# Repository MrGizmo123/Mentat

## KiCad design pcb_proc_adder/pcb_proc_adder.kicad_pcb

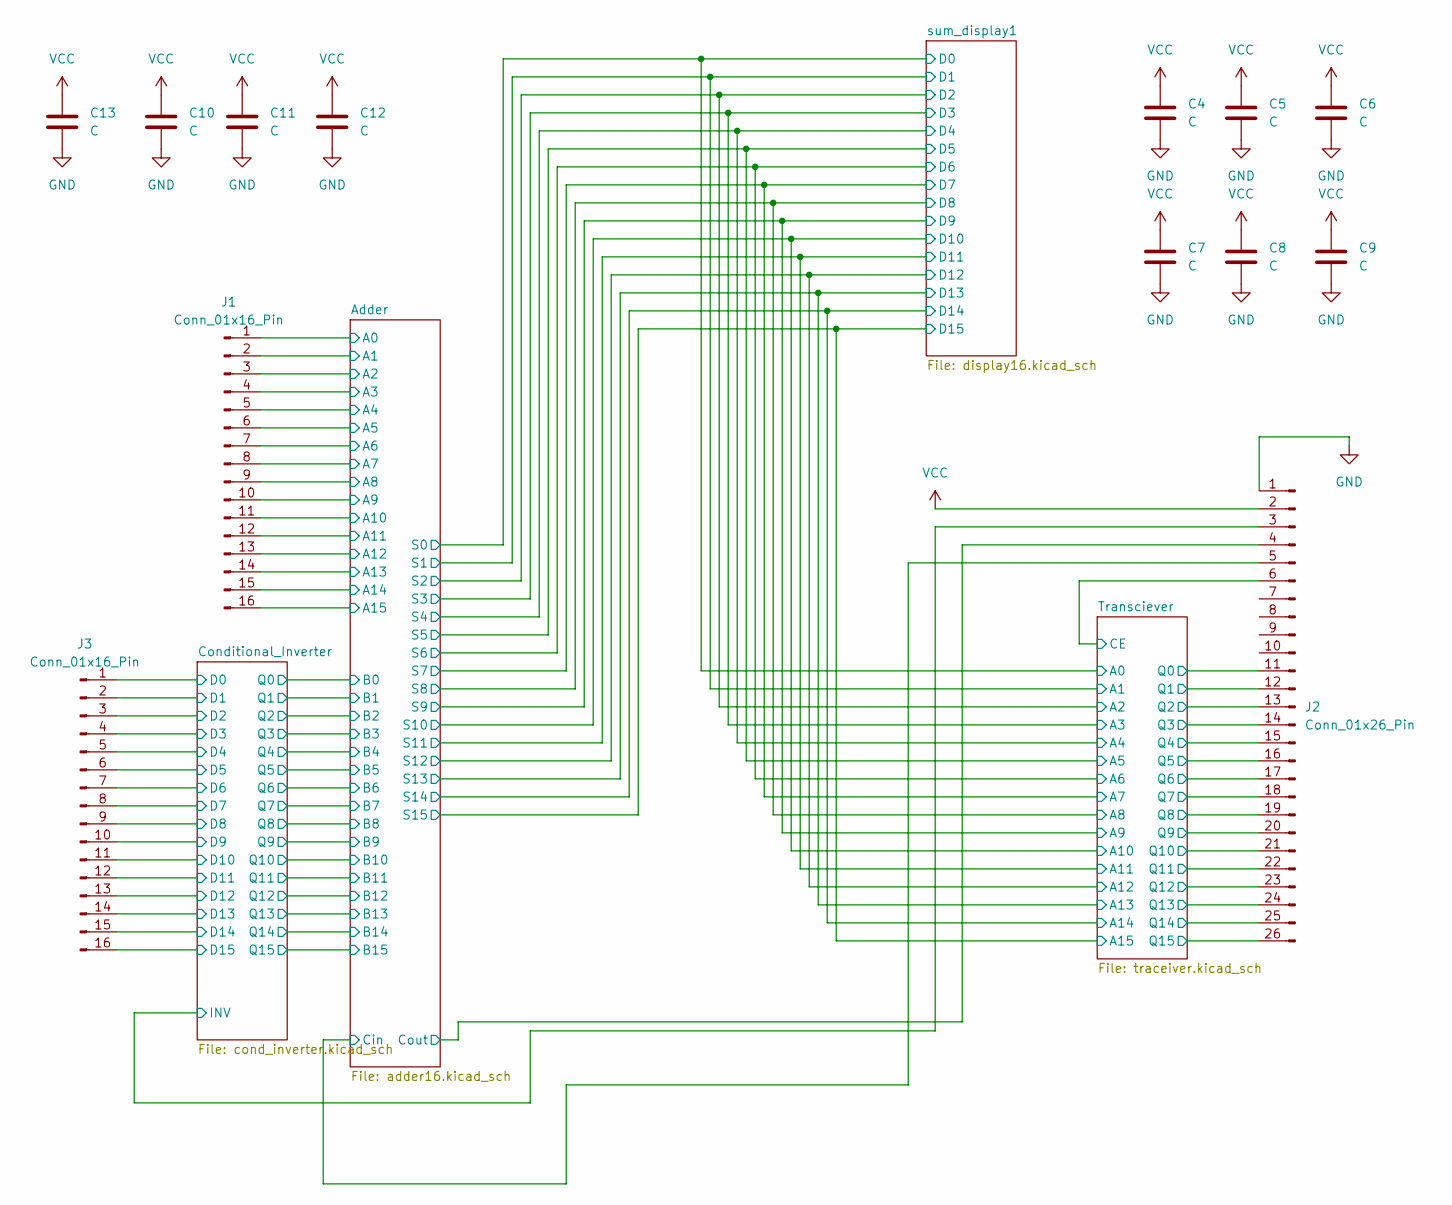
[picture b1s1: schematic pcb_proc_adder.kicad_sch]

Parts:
C4, C5, C6, C7, C8, C9, C10, C11, C12, C13: C; C_0805_2012Metric
J1, J3: Conn_01x16_Pin; PinHeader_1x16_P2.54mm_Vertical
J2: Conn_01x26_Pin; PinHeader_1x26_P2.54mm_Horizontal

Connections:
/Adder/A0: J1.1; also elsewhere on the board
/Adder/A1: J1.2; also elsewhere on the board
/Adder/A2: J1.3; also elsewhere on the board
/Adder/A3: J1.4; also elsewhere on the board
/Adder/A4: J1.5; also elsewhere on the board
/Adder/A5: J1.6; also elsewhere on the board
/Adder/A6: J1.7; also elsewhere on the board
/Adder/A7: J1.8; also elsewhere on the board
/Adder/A8: J1.9; also elsewhere on the board
/Adder/A9: J1.10; also elsewhere on the board
/Adder/A10: J1.11; also elsewhere on the board
/Adder/A11: J1.12; also elsewhere on the board
/Adder/A12: J1.13; also elsewhere on the board
/Adder/A13: J1.14; also elsewhere on the board
/Adder/A14: J1.15; also elsewhere on the board
/Adder/A15: J1.16; also elsewhere on the board
/Adder/Cin: J2.5; also elsewhere on the board
/Adder/Cout: J2.4; also elsewhere on the board
/Conditional_Inverter/D0: J3.1; also elsewhere on the board
/Conditional_Inverter/D1: J3.2; also elsewhere on the board
/Conditional_Inverter/D2: J3.3; also elsewhere on the board
/Conditional_Inverter/D3: J3.4; also elsewhere on the board
/Conditional_Inverter/D4: J3.5; also elsewhere on the board
/Conditional_Inverter/D5: J3.6; also elsewhere on the board
/Conditional_Inverter/D6: J3.7; also elsewhere on the board
/Conditional_Inverter/D7: J3.8; also elsewhere on the board
/Conditional_Inverter/D8: J3.9; also elsewhere on the board
/Conditional_Inverter/D9: J3.10; also elsewhere on the board
/Conditional_Inverter/D10: J3.11; also elsewhere on the board
/Conditional_Inverter/D11: J3.12; also elsewhere on the board
/Conditional_Inverter/D12: J3.13; also elsewhere on the board
/Conditional_Inverter/D13: J3.14; also elsewhere on the board
/Conditional_Inverter/D14: J3.15; also elsewhere on the board
/Conditional_Inverter/D15: J3.16; also elsewhere on the board
/Conditional_Inverter/INV: J2.3; also elsewhere on the board
/Transciever/CE: J2.6; also elsewhere on the board
/Transciever/Q0: J2.11; also elsewhere on the board
/Transciever/Q1: J2.12; also elsewhere on the board
/Transciever/Q2: J2.13; also elsewhere on the board
/Transciever/Q3: J2.14; also elsewhere on the board
/Transciever/Q4: J2.15; also elsewhere on the board
/Transciever/Q5: J2.16; also elsewhere on the board
/Transciever/Q6: J2.17; also elsewhere on the board
/Transciever/Q7: J2.18; also elsewhere on the board
/Transciever/Q8: J2.19; also elsewhere on the board
/Transciever/Q9: J2.20; also elsewhere on the board
/Transciever/Q10: J2.21; also elsewhere on the board
/Transciever/Q11: J2.22; also elsewhere on the board
/Transciever/Q12: J2.23; also elsewhere on the board
/Transciever/Q13: J2.24; also elsewhere on the board
/Transciever/Q14: J2.25; also elsewhere on the board
/Transciever/Q15: J2.26; also elsewhere on the board
GND: C4.2, C5.2, C6.2, C7.2, C8.2, C9.2, C10.2, C11.2, C12.2, C13.2, J2.1; also elsewhere on the board
VCC: C4.1, C5.1, C6.1, C7.1, C8.1, C9.1, C10.1, C11.1, C12.1, C13.1, J2.2; also elsewhere on the board

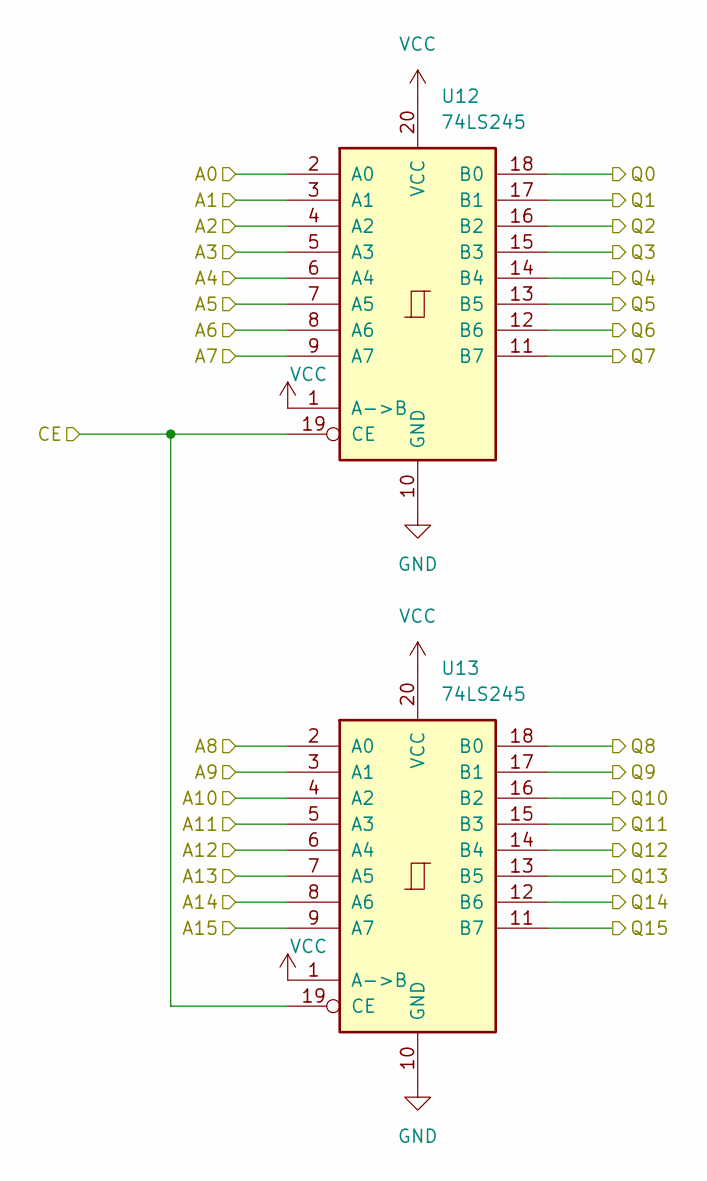
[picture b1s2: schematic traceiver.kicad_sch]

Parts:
U12, U13: 74LS245; DIP-20_W7.62mm_LongPads

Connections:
/Adder/S0: U12.2 (A0); also elsewhere on the board
/Adder/S1: U12.3 (A1); also elsewhere on the board
/Adder/S2: U12.4 (A2); also elsewhere on the board
/Adder/S3: U12.5 (A3); also elsewhere on the board
/Adder/S4: U12.6 (A4); also elsewhere on the board
/Adder/S5: U12.7 (A5); also elsewhere on the board
/Adder/S6: U12.8 (A6); also elsewhere on the board
/Adder/S7: U12.9 (A7); also elsewhere on the board
/Adder/S8: U13.2 (A0); also elsewhere on the board
/Adder/S9: U13.3 (A1); also elsewhere on the board
/Adder/S10: U13.4 (A2); also elsewhere on the board
/Adder/S11: U13.5 (A3); also elsewhere on the board
/Adder/S12: U13.6 (A4); also elsewhere on the board
/Adder/S13: U13.7 (A5); also elsewhere on the board
/Adder/S14: U13.8 (A6); also elsewhere on the board
/Adder/S15: U13.9 (A7); also elsewhere on the board
/Transciever/CE: U12.19 (CE), U13.19 (CE); also elsewhere on the board
/Transciever/Q0: U12.18 (B0); also elsewhere on the board
/Transciever/Q1: U12.17 (B1); also elsewhere on the board
/Transciever/Q2: U12.16 (B2); also elsewhere on the board
/Transciever/Q3: U12.15 (B3); also elsewhere on the board
/Transciever/Q4: U12.14 (B4); also elsewhere on the board
/Transciever/Q5: U12.13 (B5); also elsewhere on the board
/Transciever/Q6: U12.12 (B6); also elsewhere on the board
/Transciever/Q7: U12.11 (B7); also elsewhere on the board
/Transciever/Q8: U13.18 (B0); also elsewhere on the board
/Transciever/Q9: U13.17 (B1); also elsewhere on the board
/Transciever/Q10: U13.16 (B2); also elsewhere on the board
/Transciever/Q11: U13.15 (B3); also elsewhere on the board
/Transciever/Q12: U13.14 (B4); also elsewhere on the board
/Transciever/Q13: U13.13 (B5); also elsewhere on the board
/Transciever/Q14: U13.12 (B6); also elsewhere on the board
/Transciever/Q15: U13.11 (B7); also elsewhere on the board
GND: U12.10 (GND), U13.10 (GND); also elsewhere on the board
VCC: U12.1 (A->B), U12.20 (VCC), U13.1 (A->B), U13.20 (VCC); also elsewhere on the board

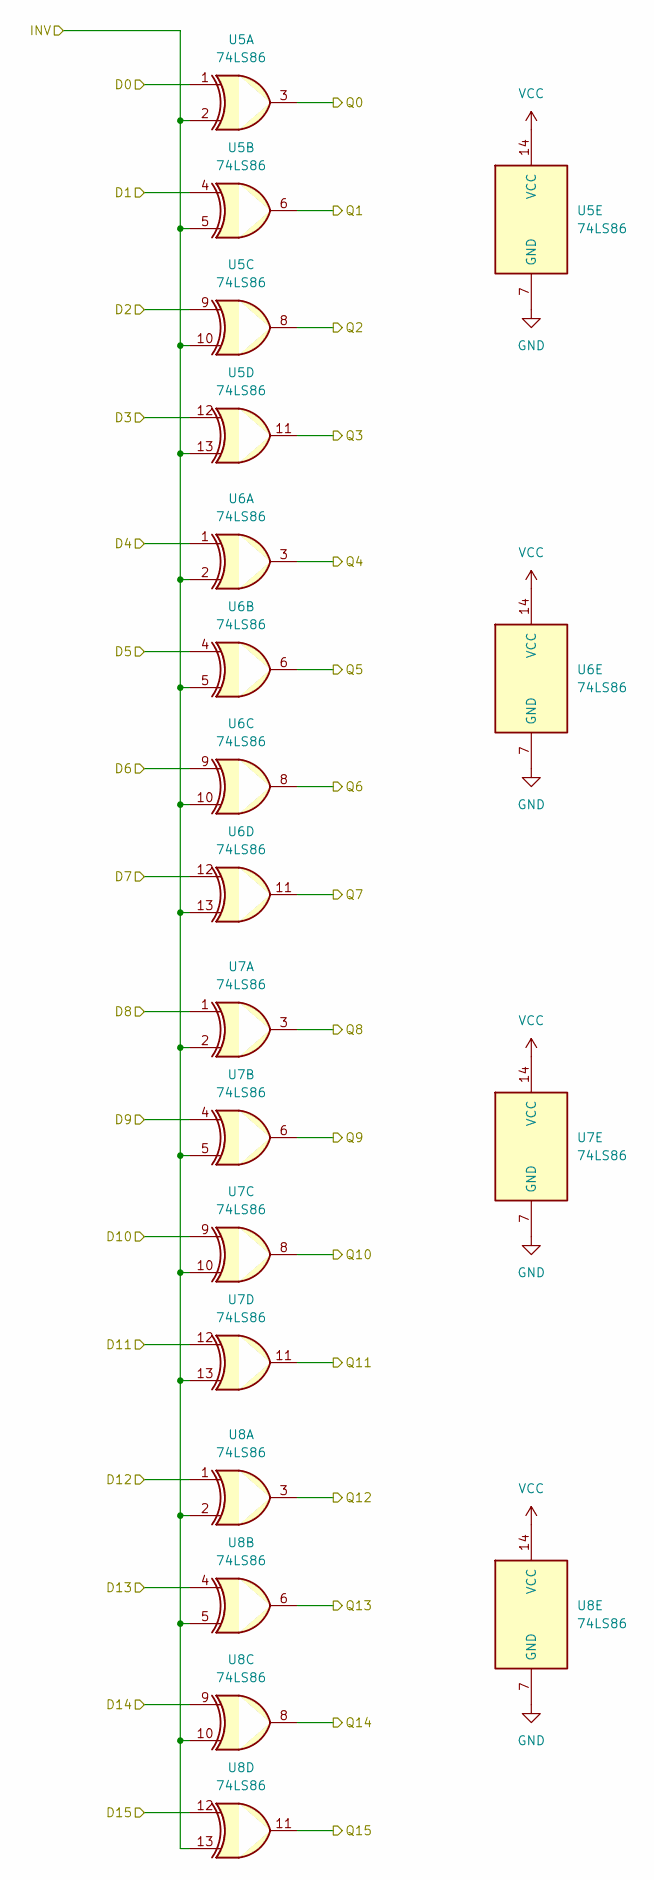
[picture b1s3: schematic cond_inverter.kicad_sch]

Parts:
U5, U6, U7, U8: 74LS86; DIP-14_W7.62mm_LongPads

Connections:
/Adder/B0: U5.3; also elsewhere on the board
/Adder/B1: U5.6; also elsewhere on the board
/Adder/B2: U5.8; also elsewhere on the board
/Adder/B3: U5.11; also elsewhere on the board
/Adder/B4: U6.3; also elsewhere on the board
/Adder/B5: U6.6; also elsewhere on the board
/Adder/B6: U6.8; also elsewhere on the board
/Adder/B7: U6.11; also elsewhere on the board
/Adder/B8: U7.3; also elsewhere on the board
/Adder/B9: U7.6; also elsewhere on the board
/Adder/B10: U7.8; also elsewhere on the board
/Adder/B11: U7.11; also elsewhere on the board
/Adder/B12: U8.3; also elsewhere on the board
/Adder/B13: U8.6; also elsewhere on the board
/Adder/B14: U8.8; also elsewhere on the board
/Adder/B15: U8.11; also elsewhere on the board
/Conditional_Inverter/D0: U5.1; also elsewhere on the board
/Conditional_Inverter/D1: U5.4; also elsewhere on the board
/Conditional_Inverter/D2: U5.9; also elsewhere on the board
/Conditional_Inverter/D3: U5.12; also elsewhere on the board
/Conditional_Inverter/D4: U6.1; also elsewhere on the board
/Conditional_Inverter/D5: U6.4; also elsewhere on the board
/Conditional_Inverter/D6: U6.9; also elsewhere on the board
/Conditional_Inverter/D7: U6.12; also elsewhere on the board
/Conditional_Inverter/D8: U7.1; also elsewhere on the board
/Conditional_Inverter/D9: U7.4; also elsewhere on the board
/Conditional_Inverter/D10: U7.9; also elsewhere on the board
/Conditional_Inverter/D11: U7.12; also elsewhere on the board
/Conditional_Inverter/D12: U8.1; also elsewhere on the board
/Conditional_Inverter/D13: U8.4; also elsewhere on the board
/Conditional_Inverter/D14: U8.9; also elsewhere on the board
/Conditional_Inverter/D15: U8.12; also elsewhere on the board
/Conditional_Inverter/INV: U5.2, U5.5, U5.10, U5.13, U6.2, U6.5, U6.10, U6.13, U7.2, U7.5, U7.10, U7.13, U8.2, U8.5, U8.10, U8.13; also elsewhere on the board
GND: U5.7 (GND), U6.7 (GND), U7.7 (GND), U8.7 (GND); also elsewhere on the board
VCC: U5.14 (VCC), U6.14 (VCC), U7.14 (VCC), U8.14 (VCC); also elsewhere on the board

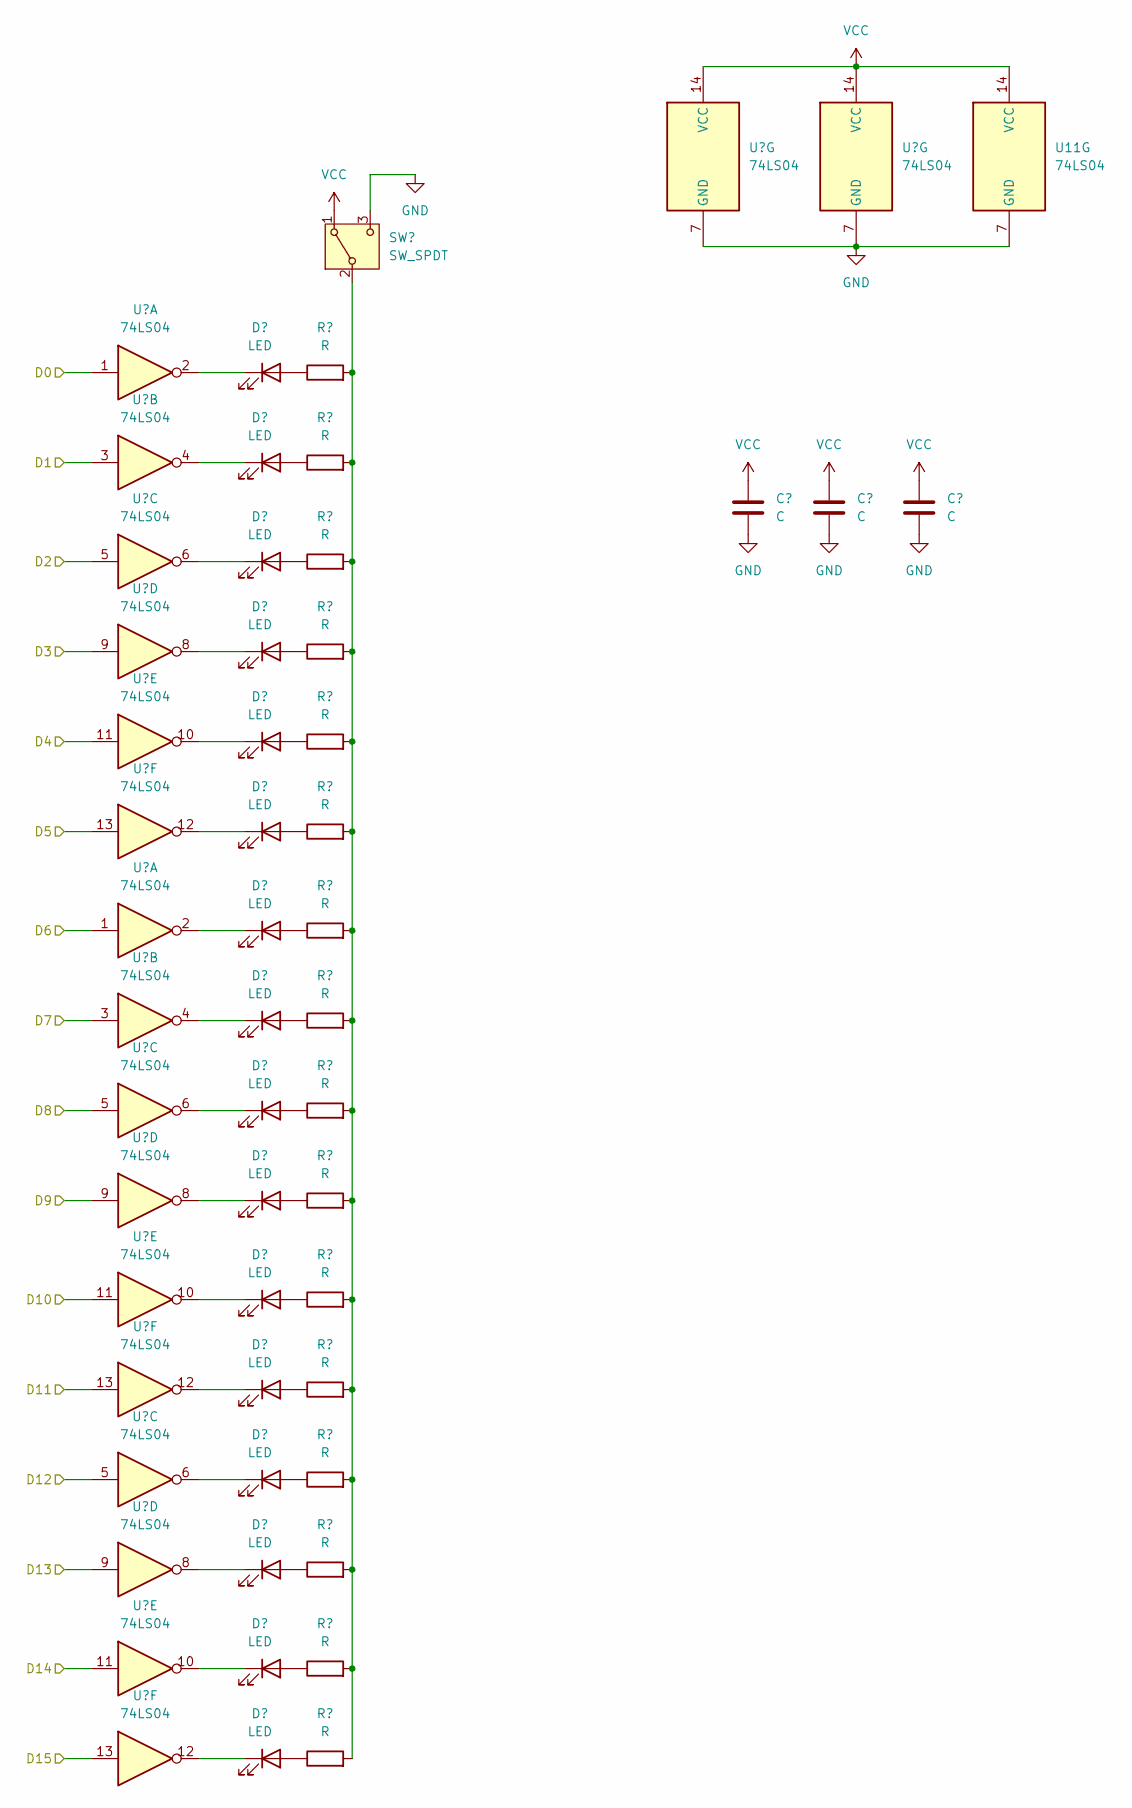
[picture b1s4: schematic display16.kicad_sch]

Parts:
C1, C2, C3: C; C_0805_2012Metric
D1, D2, D3, D4, D5, D6, D7, D8, D9, D10, D11, D12, D13, D14, D15, D16: LED; LED_Rectangular_W5.0mm_H2.0mm
R1, R2, R3, R4, R5, R6, R7, R8, R9, R10, R11, R12, R13, R14, R15, R16: R; R_0805_2012Metric
SW1: SW_SPDT; SW_E-Switch_EG1271_SPDT
U9: 74LS04; DIP-14_W7.62mm_Socket_LongPads
U10, U11: 74LS04; DIP-14_W7.62mm_LongPads

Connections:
/Adder/S0: U9.1; also elsewhere on the board
/Adder/S1: U9.3; also elsewhere on the board
/Adder/S2: U9.5; also elsewhere on the board
/Adder/S3: U9.9; also elsewhere on the board
/Adder/S4: U9.11; also elsewhere on the board
/Adder/S5: U9.13; also elsewhere on the board
/Adder/S6: U10.1; also elsewhere on the board
/Adder/S7: U10.3; also elsewhere on the board
/Adder/S8: U10.5; also elsewhere on the board
/Adder/S9: U10.9; also elsewhere on the board
/Adder/S10: U10.11; also elsewhere on the board
/Adder/S11: U10.13; also elsewhere on the board
/Adder/S12: U11.5; also elsewhere on the board
/Adder/S13: U11.9; also elsewhere on the board
/Adder/S14: U11.11; also elsewhere on the board
/Adder/S15: U11.13; also elsewhere on the board
GND: C1.2, C2.2, C3.2, SW1.3 (C), U9.7 (GND), U10.7 (GND), U11.7 (GND); also elsewhere on the board
unnamed: D1.2 (A), R1.1
unnamed: D1.1 (K), U9.2
unnamed: D2.2 (A), R2.1
unnamed: D2.1 (K), U9.4
unnamed: D3.2 (A), R3.1
unnamed: D3.1 (K), U9.6
unnamed: D4.2 (A), R4.1
unnamed: D4.1 (K), U9.8
unnamed: D5.2 (A), R5.1
unnamed: D5.1 (K), U9.10
unnamed: D6.2 (A), R6.1
unnamed: D6.1 (K), U9.12
unnamed: D7.2 (A), R7.1
unnamed: D7.1 (K), U10.2
unnamed: D8.2 (A), R8.1
unnamed: D8.1 (K), U10.4
unnamed: D9.2 (A), R9.1
unnamed: D9.1 (K), U10.6
unnamed: D10.2 (A), R10.1
unnamed: D10.1 (K), U10.8
unnamed: D11.2 (A), R11.1
unnamed: D11.1 (K), U10.10
unnamed: D12.2 (A), R12.1
unnamed: D12.1 (K), U10.12
unnamed: D13.2 (A), R13.1
unnamed: D13.1 (K), U11.6
unnamed: D14.2 (A), R14.1
unnamed: D14.1 (K), U11.8
unnamed: D15.2 (A), R15.1
unnamed: D15.1 (K), U11.10
unnamed: D16.2 (A), R16.1
unnamed: D16.1 (K), U11.12
unnamed: R1.2, R2.2, R3.2, R4.2, R5.2, R6.2, R7.2, R8.2, R9.2, R10.2, R11.2, R12.2, R13.2, R14.2, R15.2, R16.2, SW1.2 (B)
VCC: C1.1, C2.1, C3.1, SW1.1 (A), U9.14 (VCC), U10.14 (VCC), U11.14 (VCC); also elsewhere on the board

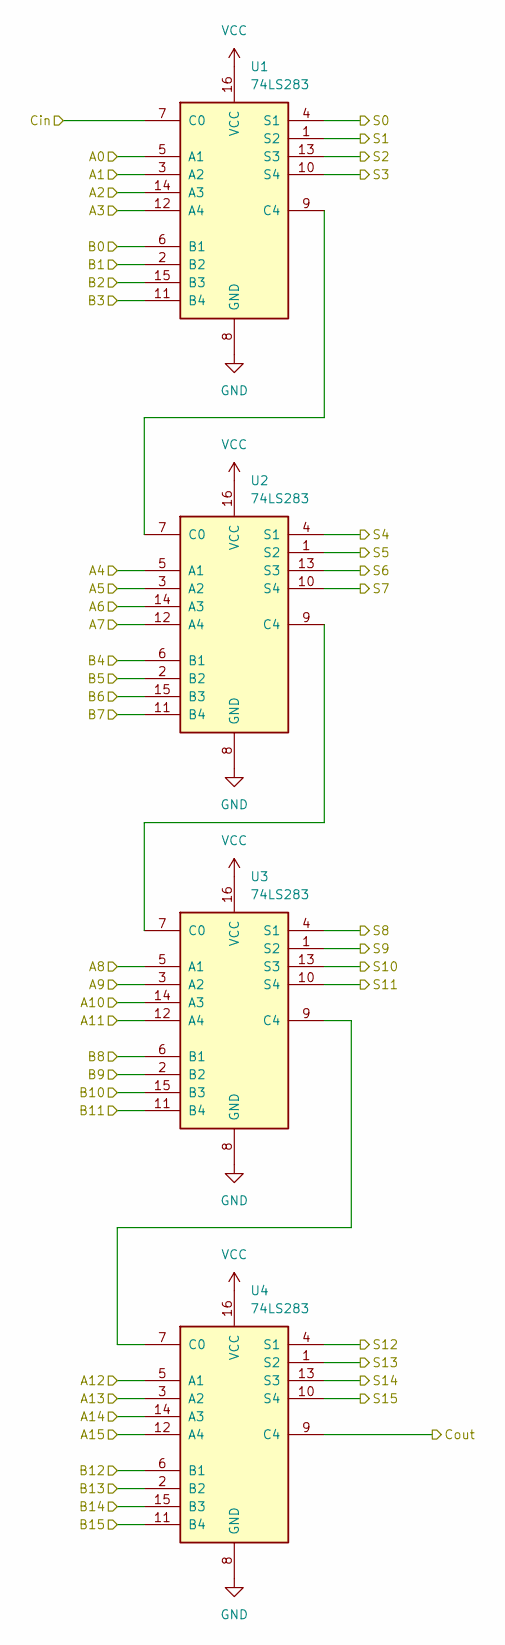
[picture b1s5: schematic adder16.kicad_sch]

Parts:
U1, U2, U3, U4: 74LS283; DIP-16_W7.62mm_LongPads

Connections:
/Adder/A0: U1.5 (A1); also elsewhere on the board
/Adder/A1: U1.3 (A2); also elsewhere on the board
/Adder/A2: U1.14 (A3); also elsewhere on the board
/Adder/A3: U1.12 (A4); also elsewhere on the board
/Adder/A4: U2.5 (A1); also elsewhere on the board
/Adder/A5: U2.3 (A2); also elsewhere on the board
/Adder/A6: U2.14 (A3); also elsewhere on the board
/Adder/A7: U2.12 (A4); also elsewhere on the board
/Adder/A8: U3.5 (A1); also elsewhere on the board
/Adder/A9: U3.3 (A2); also elsewhere on the board
/Adder/A10: U3.14 (A3); also elsewhere on the board
/Adder/A11: U3.12 (A4); also elsewhere on the board
/Adder/A12: U4.5 (A1); also elsewhere on the board
/Adder/A13: U4.3 (A2); also elsewhere on the board
/Adder/A14: U4.14 (A3); also elsewhere on the board
/Adder/A15: U4.12 (A4); also elsewhere on the board
/Adder/B0: U1.6 (B1); also elsewhere on the board
/Adder/B1: U1.2 (B2); also elsewhere on the board
/Adder/B2: U1.15 (B3); also elsewhere on the board
/Adder/B3: U1.11 (B4); also elsewhere on the board
/Adder/B4: U2.6 (B1); also elsewhere on the board
/Adder/B5: U2.2 (B2); also elsewhere on the board
/Adder/B6: U2.15 (B3); also elsewhere on the board
/Adder/B7: U2.11 (B4); also elsewhere on the board
/Adder/B8: U3.6 (B1); also elsewhere on the board
/Adder/B9: U3.2 (B2); also elsewhere on the board
/Adder/B10: U3.15 (B3); also elsewhere on the board
/Adder/B11: U3.11 (B4); also elsewhere on the board
/Adder/B12: U4.6 (B1); also elsewhere on the board
/Adder/B13: U4.2 (B2); also elsewhere on the board
/Adder/B14: U4.15 (B3); also elsewhere on the board
/Adder/B15: U4.11 (B4); also elsewhere on the board
/Adder/Cin: U1.7 (C0); also elsewhere on the board
/Adder/Cout: U4.9 (C4); also elsewhere on the board
/Adder/S0: U1.4 (S1); also elsewhere on the board
/Adder/S1: U1.1 (S2); also elsewhere on the board
/Adder/S2: U1.13 (S3); also elsewhere on the board
/Adder/S3: U1.10 (S4); also elsewhere on the board
/Adder/S4: U2.4 (S1); also elsewhere on the board
/Adder/S5: U2.1 (S2); also elsewhere on the board
/Adder/S6: U2.13 (S3); also elsewhere on the board
/Adder/S7: U2.10 (S4); also elsewhere on the board
/Adder/S8: U3.4 (S1); also elsewhere on the board
/Adder/S9: U3.1 (S2); also elsewhere on the board
/Adder/S10: U3.13 (S3); also elsewhere on the board
/Adder/S11: U3.10 (S4); also elsewhere on the board
/Adder/S12: U4.4 (S1); also elsewhere on the board
/Adder/S13: U4.1 (S2); also elsewhere on the board
/Adder/S14: U4.13 (S3); also elsewhere on the board
/Adder/S15: U4.10 (S4); also elsewhere on the board
GND: U1.8 (GND), U2.8 (GND), U3.8 (GND), U4.8 (GND); also elsewhere on the board
unnamed: U1.9 (C4), U2.7 (C0)
unnamed: U2.9 (C4), U3.7 (C0)
unnamed: U3.9 (C4), U4.7 (C0)
VCC: U1.16 (VCC), U2.16 (VCC), U3.16 (VCC), U4.16 (VCC); also elsewhere on the board

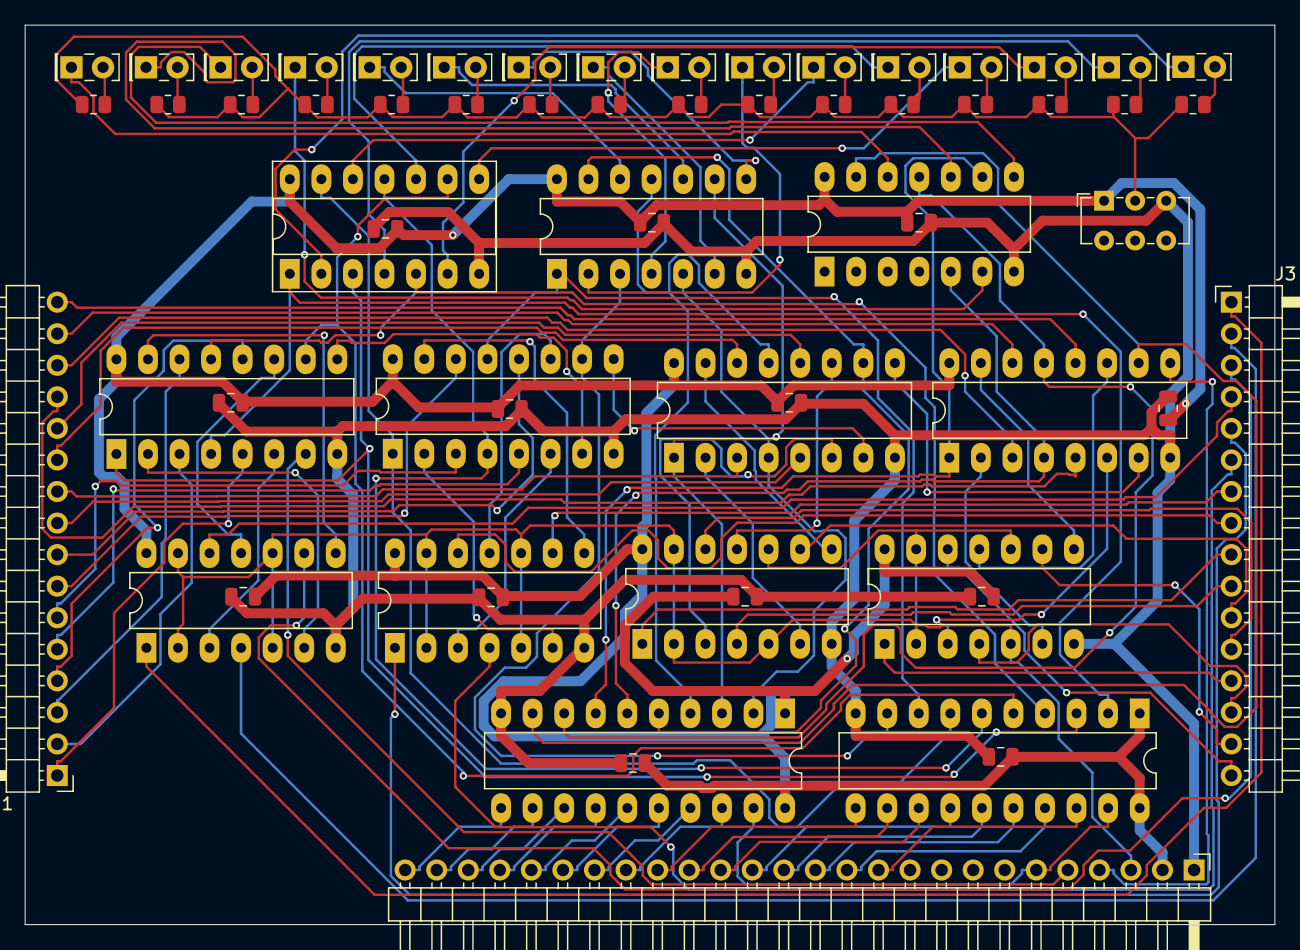
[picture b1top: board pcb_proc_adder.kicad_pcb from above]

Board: 2 copper layers, 100.6 x 72.4 mm, 62 parts (0 on the bottom side), 122 nets.

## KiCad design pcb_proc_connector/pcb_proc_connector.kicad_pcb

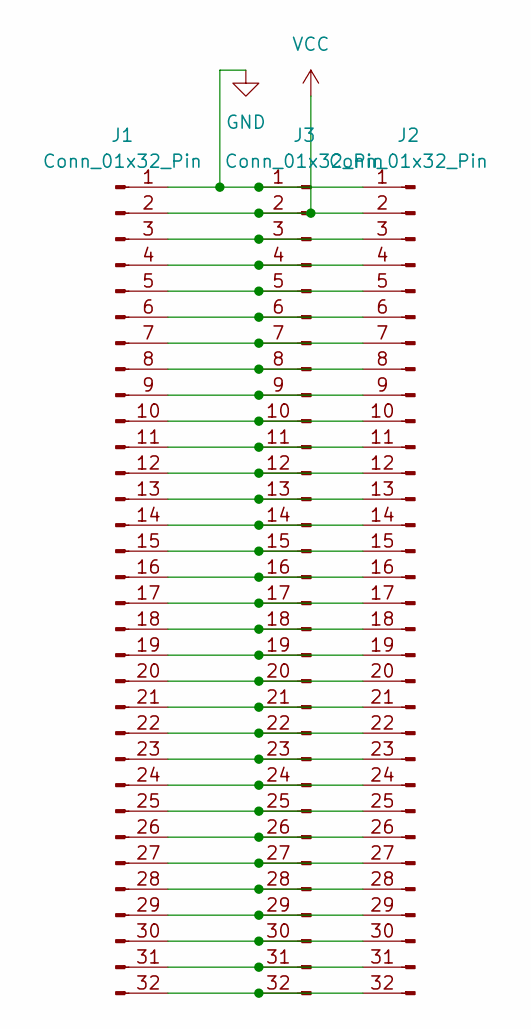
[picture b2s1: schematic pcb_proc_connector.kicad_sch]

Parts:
J1, J2, J3: Conn_01x32_Pin; PinSocket_2x16_P2.54mm_Vertical

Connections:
GND: J1.1, J2.1, J3.1
unnamed: J1.3, J2.3, J3.3
unnamed: J1.4, J2.4, J3.4
unnamed: J1.5, J2.5, J3.5
unnamed: J1.6, J2.6, J3.6
unnamed: J1.7, J2.7, J3.7
unnamed: J1.8, J2.8, J3.8
unnamed: J1.9, J2.9, J3.9
unnamed: J1.10, J2.10, J3.10
unnamed: J1.11, J2.11, J3.11
unnamed: J1.12, J2.12, J3.12
unnamed: J1.13, J2.13, J3.13
unnamed: J1.14, J2.14, J3.14
unnamed: J1.15, J2.15, J3.15
unnamed: J1.16, J2.16, J3.16
unnamed: J1.17, J2.17, J3.17
unnamed: J1.18, J2.18, J3.18
unnamed: J1.19, J2.19, J3.19
unnamed: J1.20, J2.20, J3.20
unnamed: J1.21, J2.21, J3.21
unnamed: J1.22, J2.22, J3.22
unnamed: J1.23, J2.23, J3.23
unnamed: J1.24, J2.24, J3.24
unnamed: J1.25, J2.25, J3.25
unnamed: J1.26, J2.26, J3.26
unnamed: J1.27, J2.27, J3.27
unnamed: J1.28, J2.28, J3.28
unnamed: J1.29, J2.29, J3.29
unnamed: J1.30, J2.30, J3.30
unnamed: J1.31, J2.31, J3.31
unnamed: J1.32, J2.32, J3.32
VCC: J1.2, J2.2, J3.2

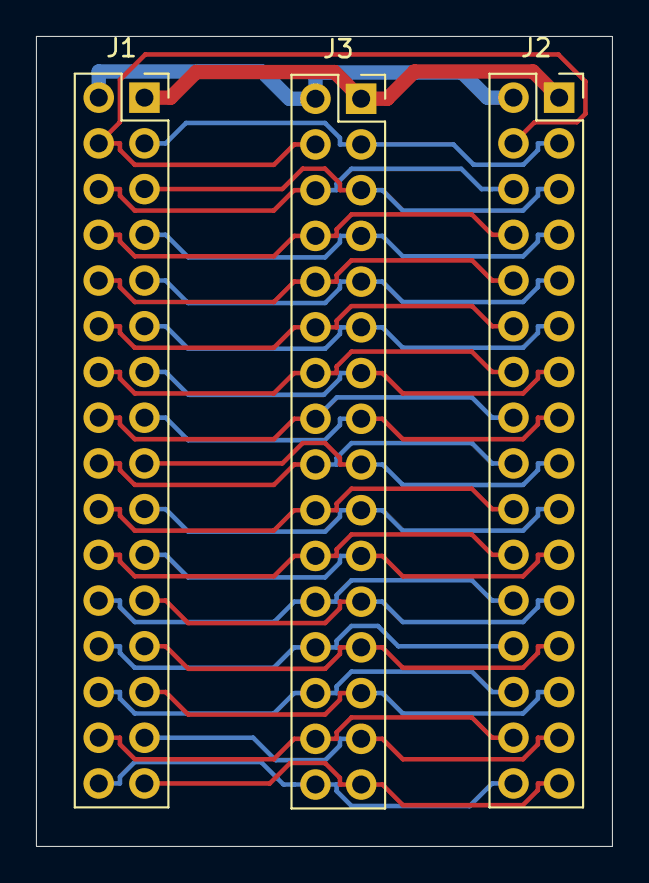
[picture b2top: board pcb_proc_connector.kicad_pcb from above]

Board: 2 copper layers, 32.0 x 45.0 mm, 3 parts (0 on the bottom side), 32 nets.
